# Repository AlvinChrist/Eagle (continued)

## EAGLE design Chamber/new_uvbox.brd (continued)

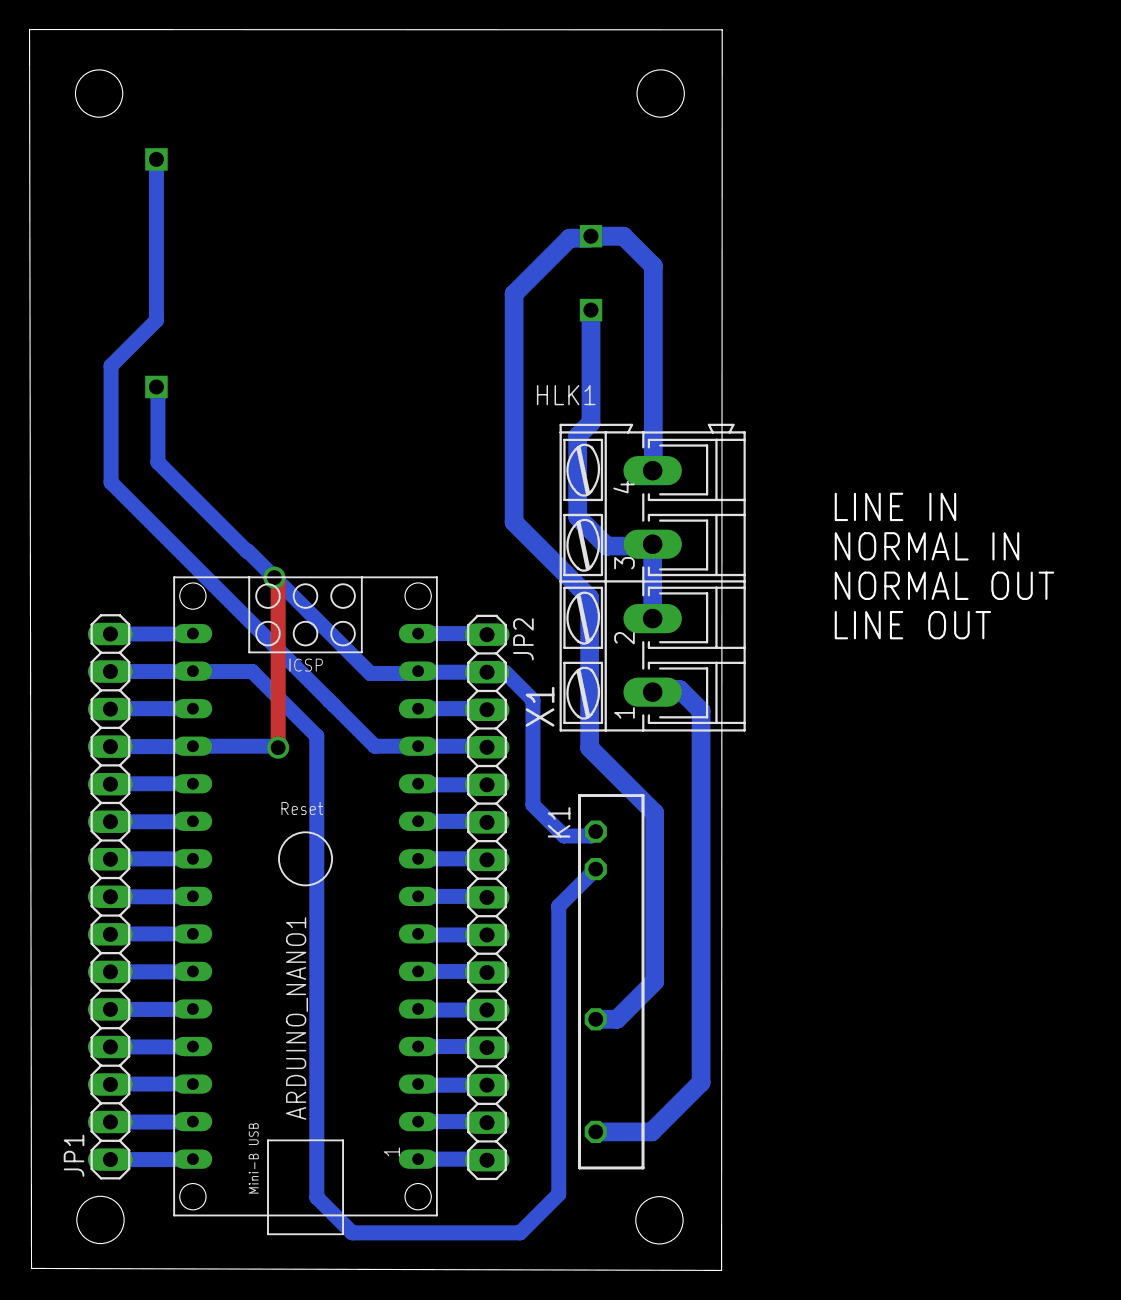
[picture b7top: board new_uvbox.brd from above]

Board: 2 copper layers, 71.8 x 84.0 mm, 6 parts (0 on the bottom side), 32 nets.

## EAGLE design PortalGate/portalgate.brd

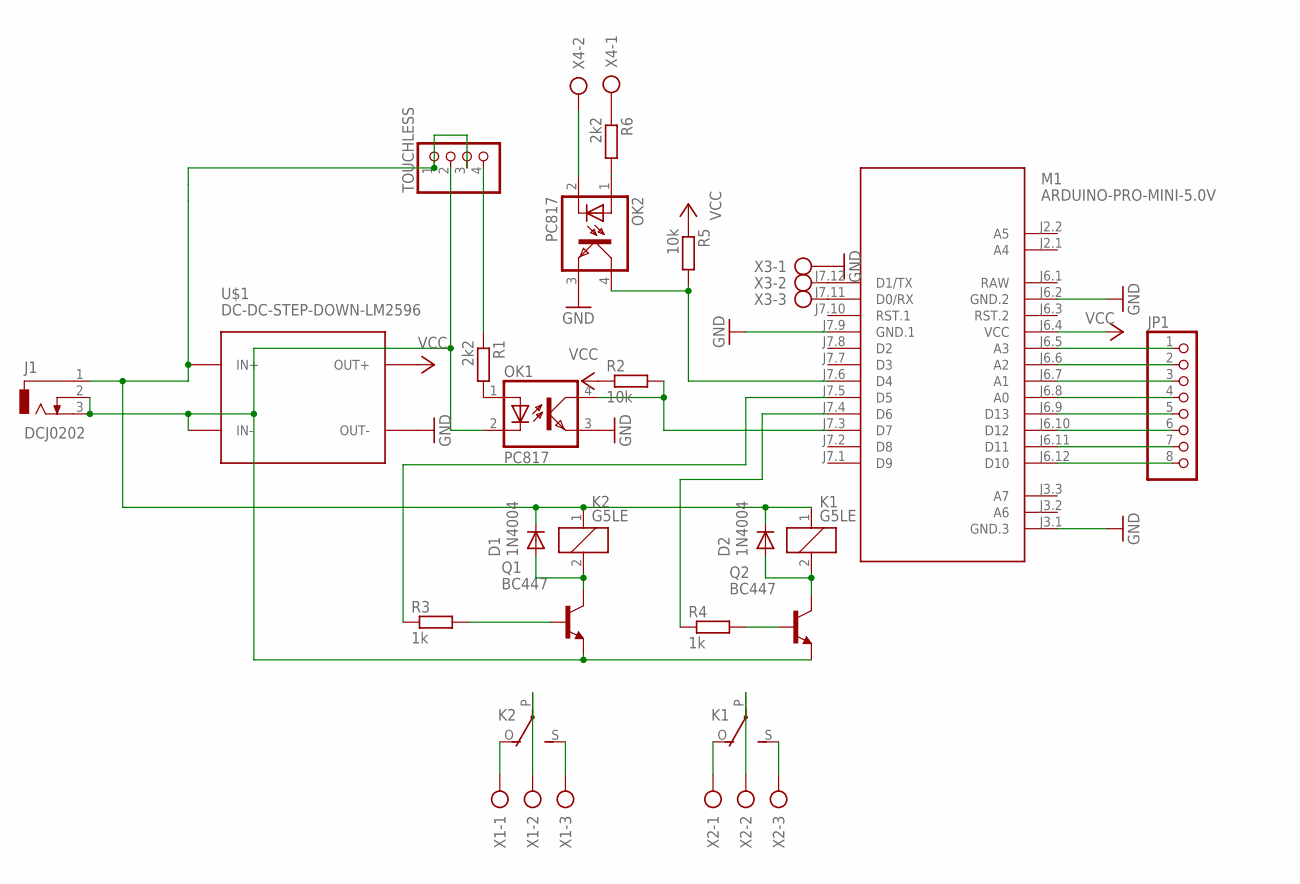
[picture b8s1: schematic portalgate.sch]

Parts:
D1, D2: 1N4004; DO41-10
J1: DCJ0202
JP1: PINHD-1X8; 1X08
K1, K2: G5LE
M1: ARDUINO-PRO-MINI-5.0V; ARDUINO-PRO-MINI
OK1, OK2: PC817; DIL04
Q1, Q2: BC447; TO92-EBC
R1, R6: 2k2; 0204/7
R2, R5: 10k; 0204/7
R3, R4: 1k; 0204/7
TOUCHLESS: PINHD-1X4; 1X04
U$1: DC-DC-STEP-DOWN-LM2596
X1, X2, X3: AK300/3
X4: AK300/2

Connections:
+12V: D1.C, D2.C, J1.1, K1.1, K2.1, TOUCHLESS.1, TOUCHLESS.3, U$1.IN+
GND: M1.J3.1 (GND.3), M1.J6.2 (GND.2), M1.J7.9 (GND.1), OK1.3 (EMIT), OK2.3 (EMIT), U$1.OUT-, X3.1
GND12V: J1.2, J1.3, OK1.2 (C), Q1.E, Q2.E, TOUCHLESS.2, U$1.IN-
unnamed: M1.J7.11 (D0/RX), X3.3
unnamed: M1.J7.12 (D1/TX), X3.2
unnamed: R1.1, TOUCHLESS.4
unnamed: OK1.1 (A), R1.2
unnamed: D2.A, K1.2, Q2.C
unnamed: M1.J7.6 (D4), OK2.4 (COL), R5.2
unnamed: M1.J7.5 (D5), R3.1
unnamed: M1.J7.4 (D6), R4.1
unnamed: Q1.B, R3.2
unnamed: JP1.1, M1.J6.5 (A3)
unnamed: K2.O, X1.1
unnamed: K2.P, X1.2
unnamed: K2.S, X1.3
unnamed: K1.P, X2.2
unnamed: K1.O, X2.1
unnamed: K1.S, X2.3
unnamed: Q2.B, R4.2
unnamed: D1.A, K2.2, Q1.C
unnamed: JP1.2, M1.J6.6 (A2)
unnamed: JP1.3, M1.J6.7 (A1)
unnamed: JP1.4, M1.J6.8 (A0)
unnamed: JP1.5, M1.J6.9 (D13)
unnamed: JP1.6, M1.J6.10 (D12)
unnamed: JP1.7, M1.J6.11 (D11)
unnamed: JP1.8, M1.J6.12 (D10)
unnamed: M1.J7.3 (D7), OK1.4 (COL), R2.2
unnamed: OK2.1 (A), R6.2
unnamed: R6.1, X4.1
unnamed: OK2.2 (C), X4.2
RAW: M1.J6.1 (RAW)
VCC: M1.J6.4 (VCC), R2.1, R5.1, U$1.OUT+

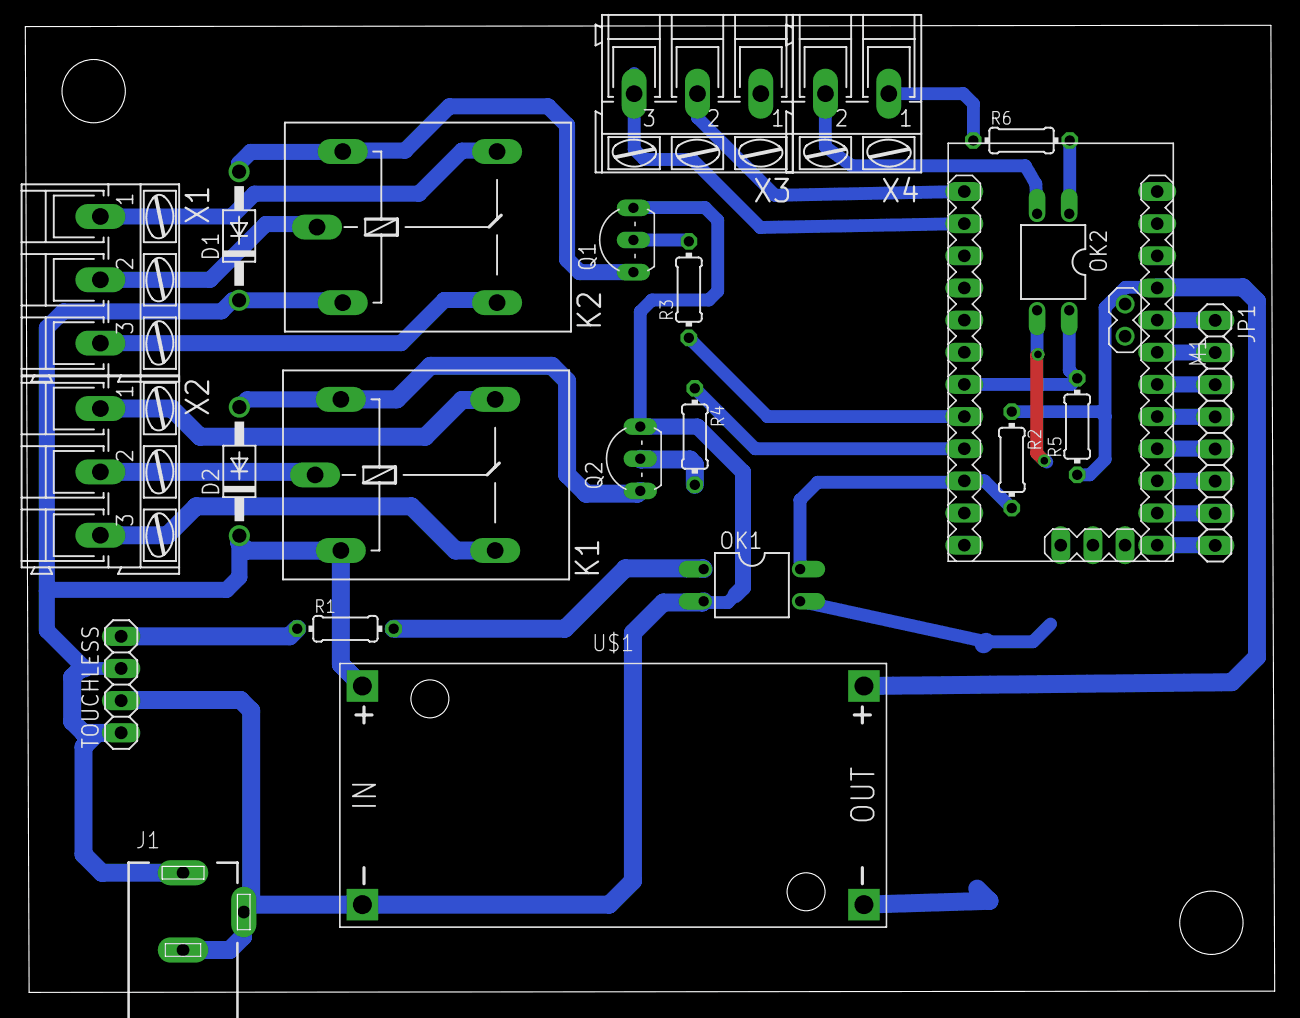
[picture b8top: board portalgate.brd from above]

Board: 2 copper layers, 98.7 x 76.4 mm, 23 parts (0 on the bottom side), 33 nets.

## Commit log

2021-06-24 Schematic Backup
